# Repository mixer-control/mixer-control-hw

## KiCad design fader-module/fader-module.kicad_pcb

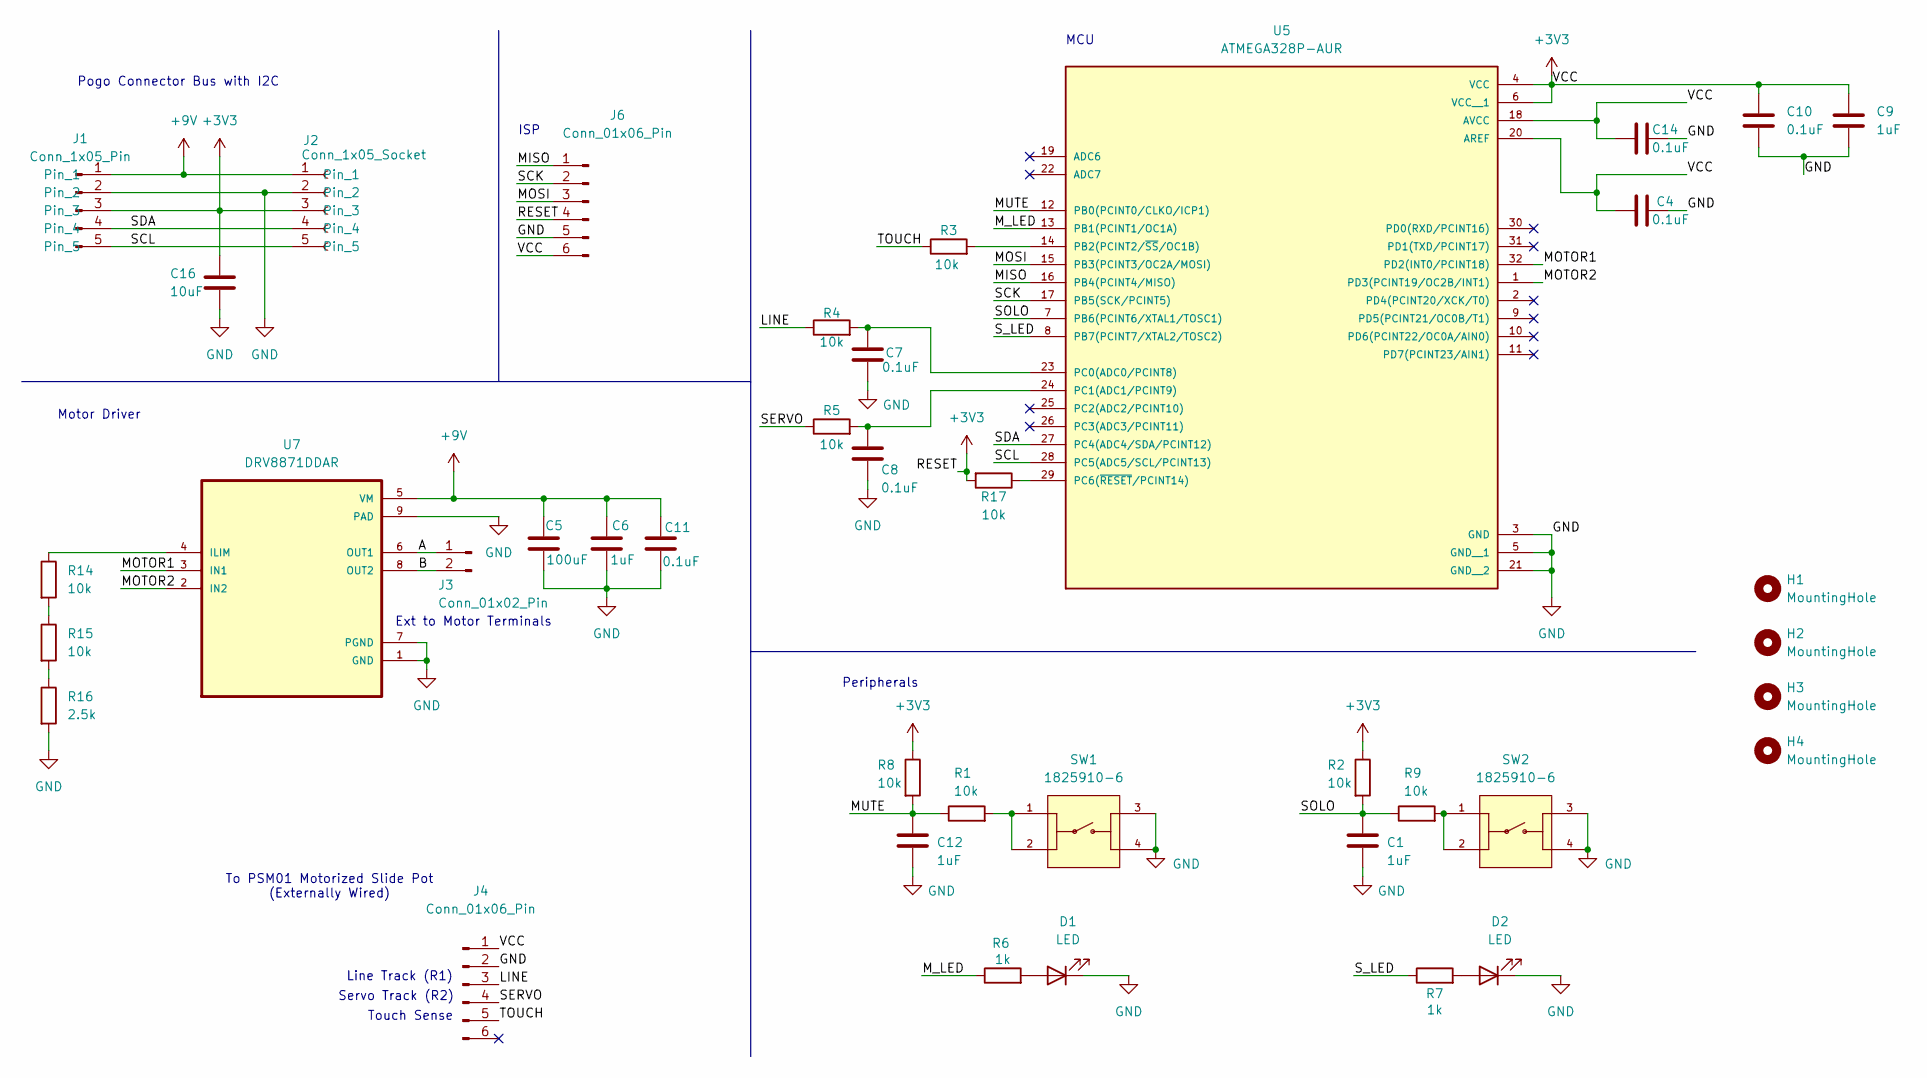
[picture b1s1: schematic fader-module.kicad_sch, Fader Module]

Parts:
C1, C6, C9, C12: 1uF; C_0805_2012Metric_Pad1.18x1.45mm_HandSolder
C4, C7, C8, C10, C11, C14: 0.1uF; C_0805_2012Metric_Pad1.18x1.45mm_HandSolder
C5: 100uF; C_1206_3216Metric_Pad1.33x1.80mm_HandSolder
C16: 10uF; C_0805_2012Metric_Pad1.18x1.45mm_HandSolder
D1, D2: LED; Molex_KK-254_AE-6410-02A_1x02_P2.54mm_Vertical
H1, H2, H3, H4: MountingHole; MountingHole_3.2mm_M3
J1: Conn_1x05_Pin; MG05254-M-RA-1N1S
J2: Conn_1x05_Socket; MG05254-M-RA-1N1S
J3: Conn_01x02_Pin; TerminalBlock_Phoenix_MKDS-1,5-2-5.08_1x02_P5.08mm_Horizont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
J4, J6: Conn_01x06_Pin; IDC-Header_2x03_P2.54mm_Vertical
R1, R2, R3, R4, R5, R8, R9, R14, R15, R17: 10k; R_0805_2012Metric_Pad1.20x1.40mm_HandSolder
R6, R7: 1k; R_0805_2012Metric_Pad1.20x1.40mm_HandSolder
R16: 2.5k; R_0805_2012Metric_Pad1.20x1.40mm_HandSolder
SW1, SW2: 1825910-6; SW_1825910-6-4; PARTREV C10
U5: ATMEGA328P-AUR; QFP80P900X900X120-32N; PARTREV A
U7: DRV8871DDAR; VREG_LM5017MR_NOPB

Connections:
+3V3: C4.1, C9.1, C10.1, C14.1, C16.1, J1.3, J2.3, J4.1, J6.4, J6.6, R2.1, R8.1, R17.2, U5.4 (VCC), U5.6 (VCC__1), U5.18 (AVCC), U5.20 (AREF)
+9V: C5.1, C6.1, C11.1, J1.1, J2.1, U7.5 (VM)
/A: J3.1, U7.6 (OUT1)
/B: J3.2, U7.8 (OUT2)
/LINE: J4.3, R4.1
/MISO: J6.1, U5.16 (PB4(PCINT4/MISO))
/MOSI: J6.3, U5.15 (PB3(PCINT3/OC2A/MOSI))
/MOTOR1: U5.32 (PD2(INT0/PCINT18)), U7.3 (IN1)
/MOTOR2: U5.1 (PD3(PCINT19/OC2B/INT1)), U7.2 (IN2)
/MUTE: C12.1, R1.1, R8.2, U5.12 (PB0(PCINT0/CLKO/ICP1))
/M_LED: R6.1, U5.13 (PB1(PCINT1/OC1A))
/SCK: J6.2, U5.17 (PB5(SCK/PCINT5))
/SCL: J1.5, J2.5, U5.28 (PC5(ADC5/SCL/PCINT13))
/SDA: J1.4, J2.4, U5.27 (PC4(ADC4/SDA/PCINT12))
/SERVO: J4.4, R5.1
/SOLO: C1.1, R2.2, R9.1, U5.7 (PB6(PCINT6/XTAL1/TOSC1))
/S_LED: R7.1, U5.8 (PB7(PCINT7/XTAL2/TOSC2))
/TOUCH: J4.5, R3.1
GND: C1.2, C4.2, C5.2, C6.2, C7.1, C8.2, C9.2, C10.2, C11.2, C12.2, C14.2, C16.2, D1.1 (K), D2.1 (K), J1.2, J2.2, J4.2, J6.5, R16.2, SW1.3, SW1.4, SW2.3, SW2.4, U5.3 (GND), U5.5 (GND__1), U5.21 (GND__2), U7.1 (GND), U7.7 (PGND), U7.9 (PAD), U7.10, U7.11, U7.12, U7.13, U7.14, U7.15, U7.16, U7.17
unnamed: D1.2 (A), R6.2
unnamed: D2.2 (A), R7.2
unnamed: R1.2, SW1.1, SW1.2
unnamed: R9.2, SW2.1, SW2.2
unnamed: R14.2, R15.1
unnamed: R15.2, R16.1
unnamed: R3.2, U5.14 (PB2(PCINT2/~SS/OC1B))
unnamed: C7.2, R4.2, U5.23 (PC0(ADC0/PCINT8))
unnamed: C8.1, R5.2, U5.24 (PC1(ADC1/PCINT9))
unnamed: R17.1, U5.29 (PC6(~RESET/PCINT14))
unnamed: R14.1, U7.4 (ILIM)

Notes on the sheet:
MCU
Touch Sense
Servo Track (R2)
Pogo Connector Bus with I2C
Ext to Motor Terminals
To PSM01 Motorized Slide Pot (Externally Wired)
Line Track (R1)
Peripherals
ISP
Motor Driver

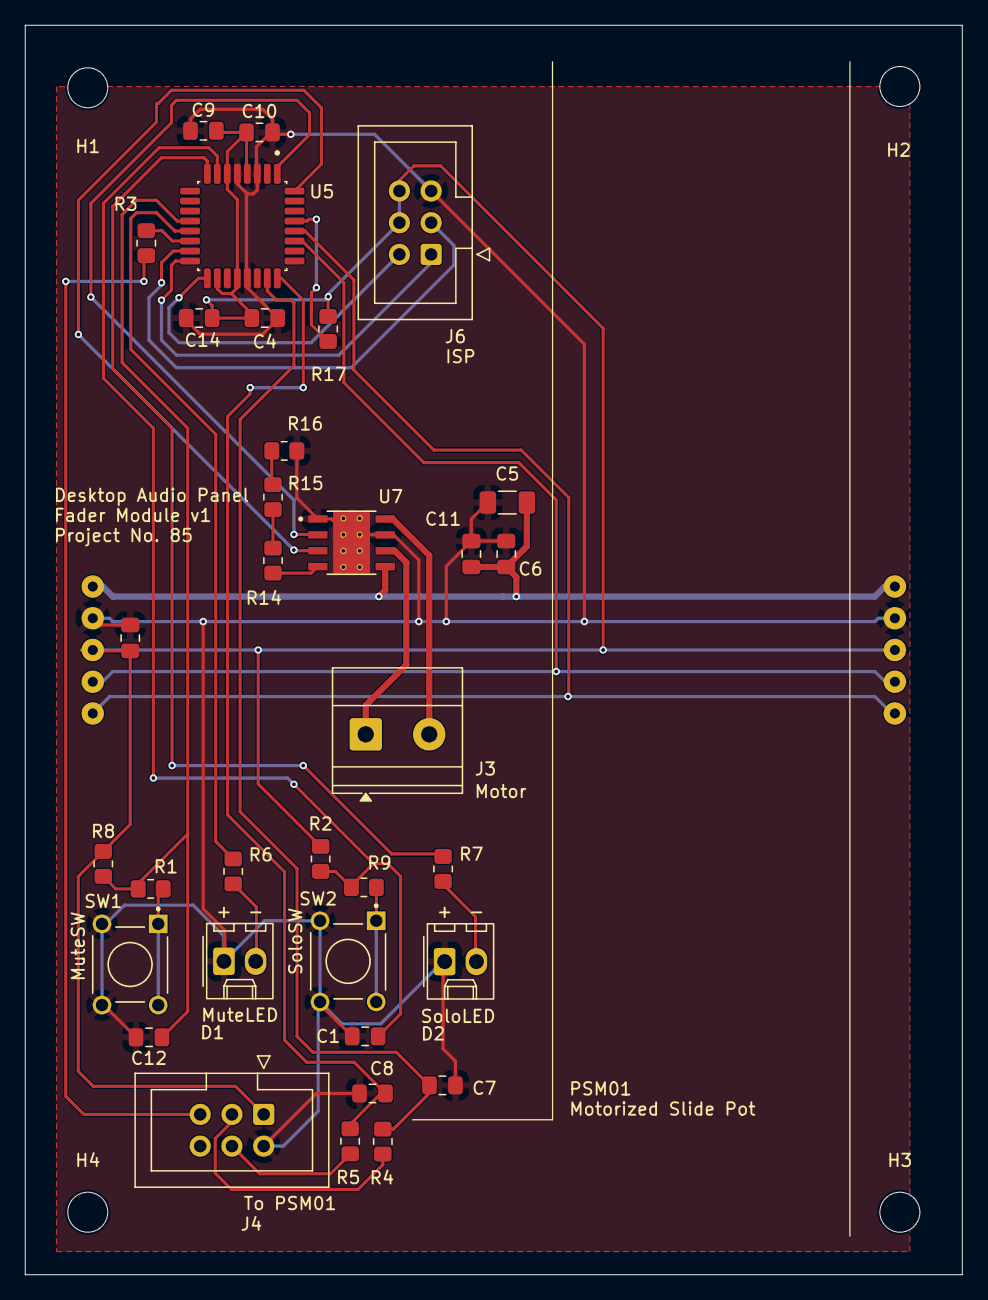
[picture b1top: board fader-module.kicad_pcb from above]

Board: 2 copper layers, 75.0 x 100.0 mm, 40 parts (0 on the bottom side), 30 nets.

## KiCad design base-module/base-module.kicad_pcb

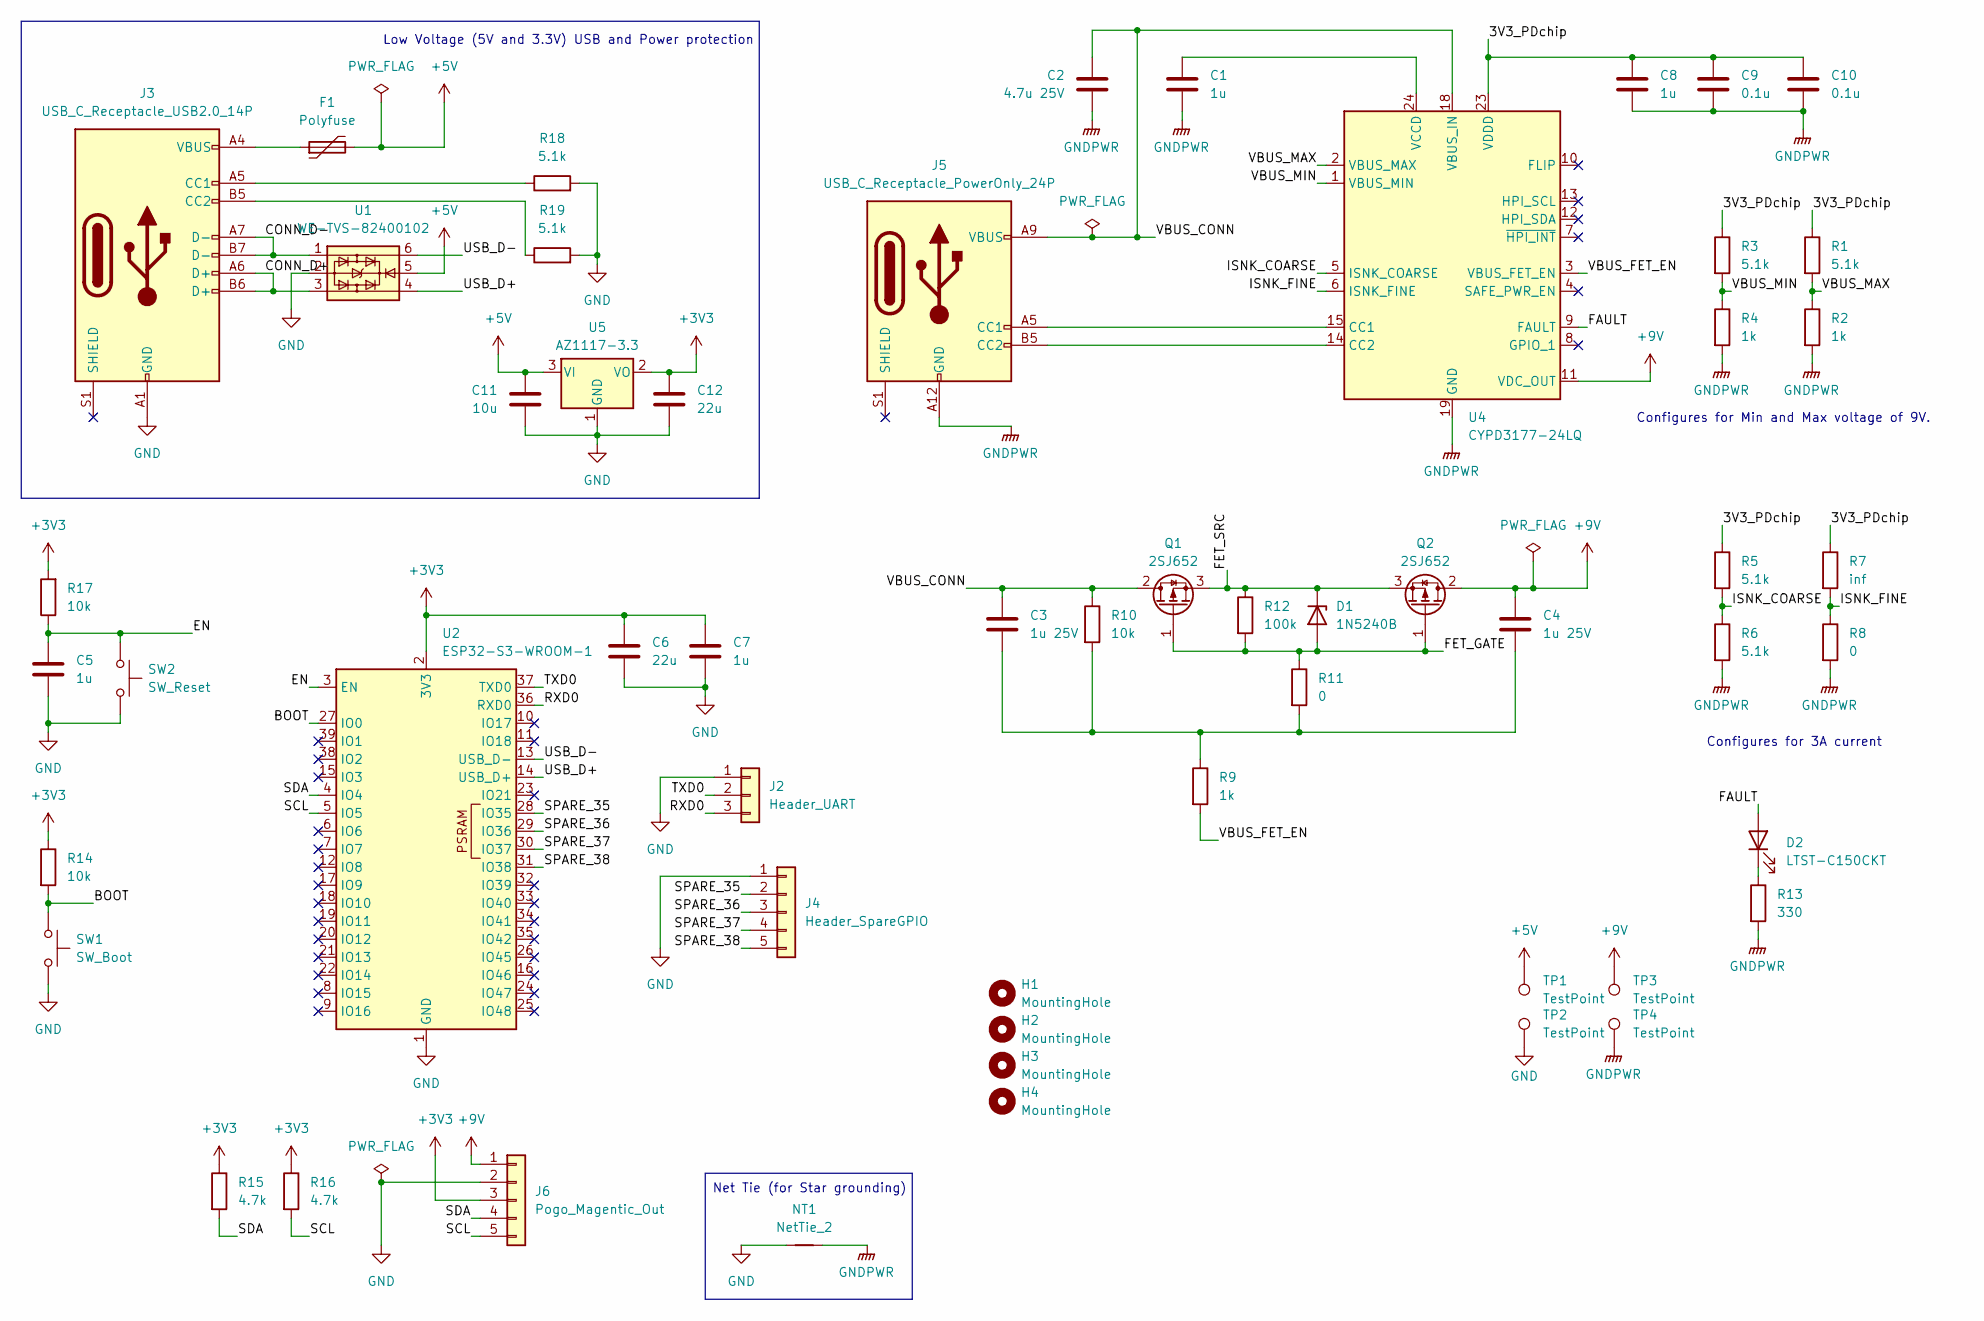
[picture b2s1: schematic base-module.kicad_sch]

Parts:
C1, C5, C7, C8: 1u; C_0805_2012Metric_Pad1.18x1.45mm_HandSolder
C2: 4.7u 25V; C_0805_2012Metric_Pad1.18x1.45mm_HandSolder
C3, C4: 1u 25V; C_0805_2012Metric_Pad1.18x1.45mm_HandSolder
C6, C12: 22u; C_0805_2012Metric_Pad1.18x1.45mm_HandSolder
C9, C10: 0.1u; C_0805_2012Metric_Pad1.18x1.45mm_HandSolder
C11: 10u; C_0805_2012Metric_Pad1.18x1.45mm_HandSolder
D1: 1N5240B; D_DO-35_SOD27_P7.62mm_Horizontal
D2: LTST-C150CKT; LED_1206_3216Metric
F1: Polyfuse; R_1206_3216Metric
H1, H2, H3, H4: MountingHole; MountingHole_3.2mm_M3
J2: Header_UART; PinHeader_1x03_P2.54mm_Vertical
J3: USB_C_Receptacle_USB2.0_14P; USB_C_Receptacle_GCT_USB4085
J4: Header_SpareGPIO; PinHeader_1x05_P2.54mm_Vertical
J5: USB_C_Receptacle_PowerOnly_24P; USB_C_Receptacle_GCT_USB4085
J6: Pogo_Magentic_Out; PinHeader_1x05_P2.54mm_Vertical
NT1: NetTie_2; NetTie-2_SMD_Pad2.0mm
Q1, Q2: 2SJ652; TO-220F-3_Vertical
R1, R3, R5, R6, R18, R19: 5.1k; R_0805_2012Metric_Pad1.20x1.40mm_HandSolder
R2, R4, R9: 1k; R_0805_2012Metric_Pad1.20x1.40mm_HandSolder
R7: inf; R_0805_2012Metric_Pad1.20x1.40mm_HandSolder
R8, R11: 0; R_0805_2012Metric_Pad1.20x1.40mm_HandSolder
R10, R14, R17: 10k; R_0805_2012Metric_Pad1.20x1.40mm_HandSolder
R12: 100k; R_0805_2012Metric_Pad1.20x1.40mm_HandSolder
R13: 330; R_0805_2012Metric_Pad1.20x1.40mm_HandSolder
R15, R16: 4.7k; R_1206_3216Metric_Pad1.30x1.75mm_HandSolder
SW1: SW_Boot; SW_PUSH_6mm
SW2: SW_Reset; SW_PUSH_6mm
TP1, TP2, TP3, TP4: TestPoint; TestPoint_Loop_D2.50mm_Drill1.0mm
U1: WE-TVS-82400102; SOT-23-6
U2: ESP32-S3-WROOM-1
U4: CYPD3177-24LQ; QFN-24-1EP_4x4mm_P0.5mm_EP2.75x2.75mm_ThermalVias
U5: AZ1117-3.3; TO-252-2

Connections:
+3V3: C6.1, C7.1, C12.1, J6.3, R14.1, R15.1, R16.1, R17.2, U2.2 (3V3), U5.2 (VO)
+5V: C11.1, F1.2, TP1.1 (1_1), U1.5, U5.3 (VI)
+9V: C4.1, J6.1, Q2.2 (D), TP3.1 (1_1), U4.11 (VDC_OUT)
/3V3_PDchip: C8.1, C9.1, C10.1, R1.1, R3.1, R5.1, R7.1, U4.23 (VDDD)
/BOOT: R14.2, SW1.1, U2.27 (IO0)
/CONN_D+: J3.A6 (D+), J3.B6 (D+), U1.3
/CONN_D-: J3.A7 (D-), J3.B7 (D-), U1.1
/EN: C5.1, R17.1, SW2.1, U2.3 (EN)
/FAULT: D2.2 (A), U4.9 (FAULT)
/FET_GATE: D1.2 (A), Q1.1 (G), Q2.1 (G), R11.1, R12.2
/FET_SRC: D1.1 (K), Q1.3 (S), Q2.3 (S), R12.1
/ISNK_COARSE: R5.2, R6.1, U4.5 (ISNK_COARSE)
/ISNK_FINE: R7.2, R8.1, U4.6 (ISNK_FINE)
/RXD0: J2.3, U2.36 (RXD0)
/SCL: J6.5, R16.2, U2.5 (IO5)
/SDA: J6.4, R15.2, U2.4 (IO4)
/SPARE_35: J4.2, U2.28 (IO35)
/SPARE_36: J4.3, U2.29 (IO36)
/SPARE_37: J4.4, U2.30 (IO37)
/SPARE_38: J4.5, U2.31 (IO38)
/TXD0: J2.2, U2.37 (TXD0)
/USB_D+: U1.4, U2.14 (USB_D+)
/USB_D-: U1.6, U2.13 (USB_D-)
/VBUS_CONN: C2.1, C3.1, J5.A4 (VBUS), J5.A9 (VBUS), J5.B4 (VBUS), J5.B9 (VBUS), Q1.2 (D), R10.1, U4.18 (VBUS_IN)
/VBUS_FET_EN: R9.2, U4.3 (VBUS_FET_EN)
/VBUS_MAX: R1.2, R2.1, U4.2 (VBUS_MAX)
/VBUS_MIN: R3.2, R4.1, U4.1 (VBUS_MIN)
GND: C5.2, C6.2, C7.2, C11.2, C12.2, J2.1, J3.A1 (GND), J3.A12 (GND), J3.B1 (GND), J3.B12 (GND), J4.1, J6.2, NT1.1, R18.2, R19.2, SW1.2, SW2.2, TP2.1 (1_1), U1.2, U2.1 (GND), U2.40 (GND), U2.41 (GND), U5.1 (GND)
GNDPWR: C1.2, C2.2, C8.2, C9.2, C10.2, J5.A1 (GND), J5.A12 (GND), J5.B1 (GND), J5.B12 (GND), NT1.2, R2.2, R4.2, R6.2, R8.2, R13.2, TP4.1 (1_1), U4.19 (GND), U4.22 (GND), U4.25 (GND)
unnamed: C3.2, C4.2, R9.1, R10.2, R11.2
unnamed: D2.1 (K), R13.1
unnamed: F1.1, J3.A4 (VBUS), J3.A9 (VBUS), J3.B4 (VBUS), J3.B9 (VBUS)
unnamed: J3.A5 (CC1), R18.1
unnamed: J3.B5 (CC2), R19.1
unnamed: J5.A5 (CC1), U4.15 (CC1)
unnamed: J5.B5 (CC2), U4.14 (CC2)
unnamed: C1.1, U4.24 (VCCD)

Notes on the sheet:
Low Voltage (5V and 3.3V) USB and Power protection
Configures for Min and Max voltage of 9V.
Configures for 3A current
Net Tie (for Star grounding)

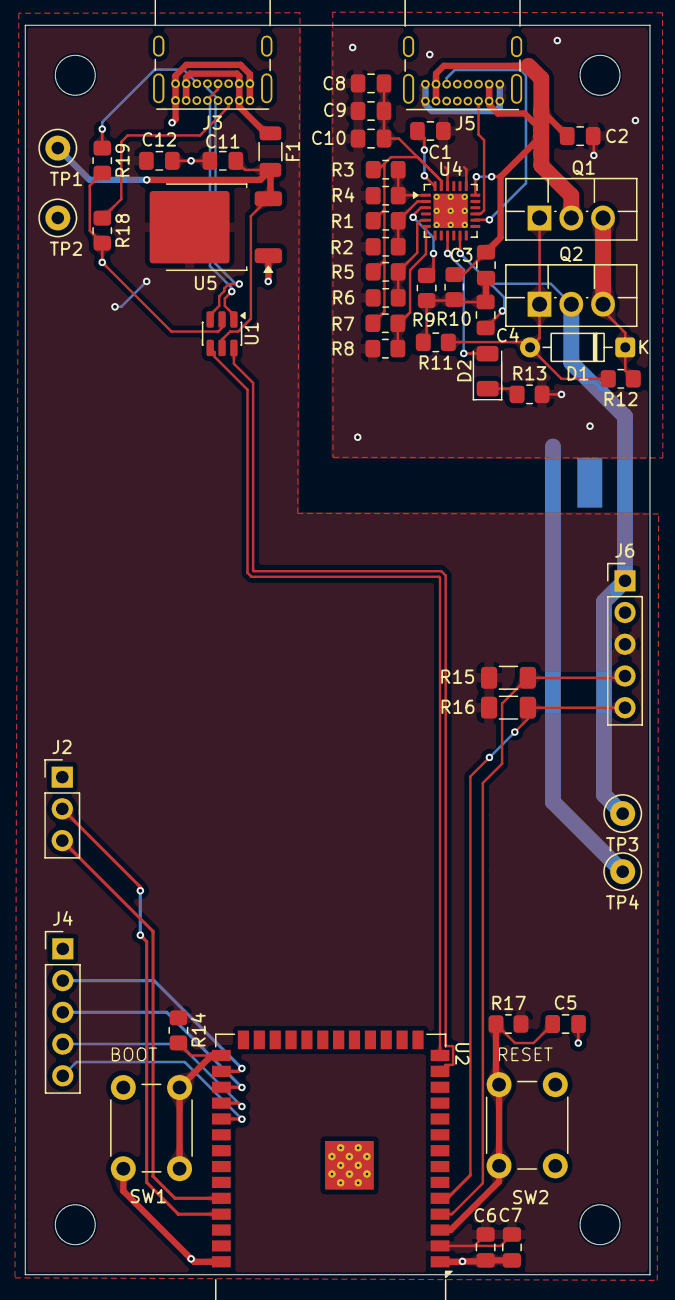
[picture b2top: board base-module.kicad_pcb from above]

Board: 2 copper layers, 50.0 x 100.0 mm, 56 parts (1 on the bottom side), 37 nets.

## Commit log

2026-03-12 symbol libs
2026-03-12 dsstore to gitignore
2026-03-12 clean psm sym
2026-03-12 schematic almost done... the hard part is still in front of us still need to add tantalum or electrolytic caps to output of LD1117
2026-03-12 fader module wip
    wtf is decoupling
2026-03-12 complete
2026-03-12 wip fader wip
2026-03-12 wip fader wip wip
2026-03-12 reorg fader
2026-03-12 finish fader
2026-03-12 symbol libs + fader tweaks
2026-03-12 lib-tales
2026-03-12 lines and whatnot
2026-03-13 footprint etc lib updates
2026-03-13 assigned footprints sans pogo
2026-03-13 finish footprints
2026-03-13 move fader module to new project
2026-03-13 fader begin route except i forgot widths anyways theyre mostly laid out the components i mean
2026-03-14 HHHHAAAAHHHHH traces AHH
2026-03-14 gotta add connector for motor prob LMAO
    also do i need 9v caps??
2026-03-24 i will combust
2026-03-25 finished routing
2026-03-25 eRrOr FrOnT sOlDeR mAsK
2026-03-25 done w pcb gerbert time
2026-03-26 the fuckin u7 clearance is acting up again
    i also forgot how to wire a button LOL
2026-03-26 ok i fixed it
2026-03-26 aligned mounting holes
2026-03-26 gerbert
2026-03-26 gerbert zip
